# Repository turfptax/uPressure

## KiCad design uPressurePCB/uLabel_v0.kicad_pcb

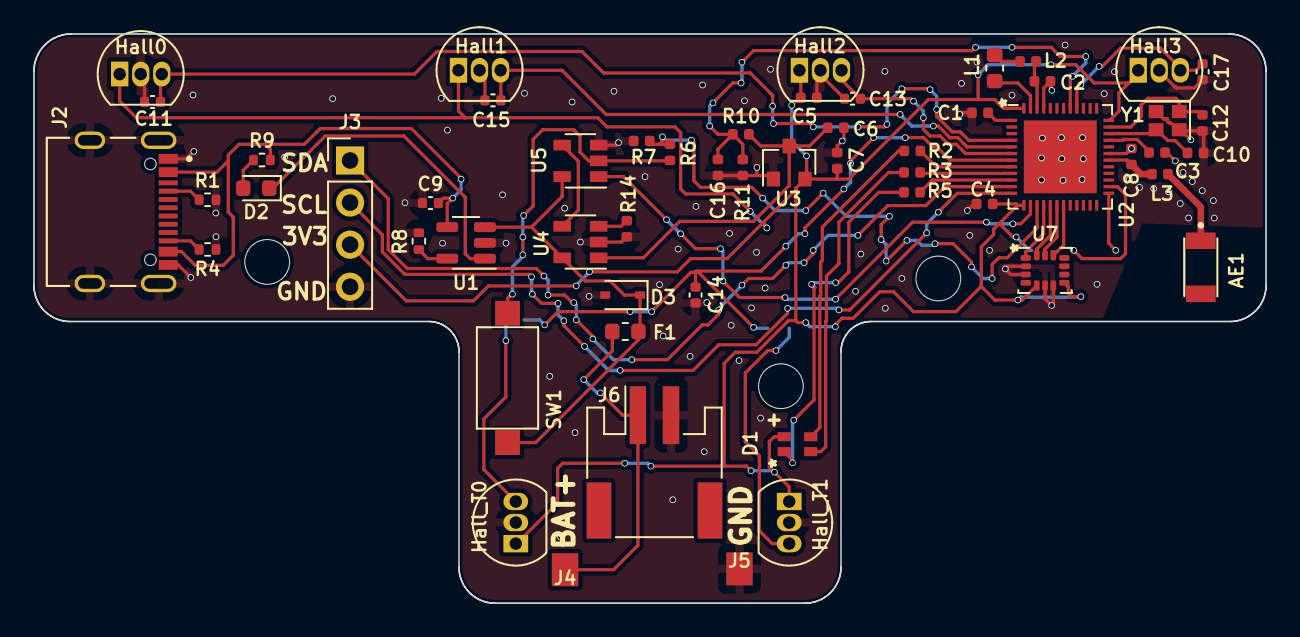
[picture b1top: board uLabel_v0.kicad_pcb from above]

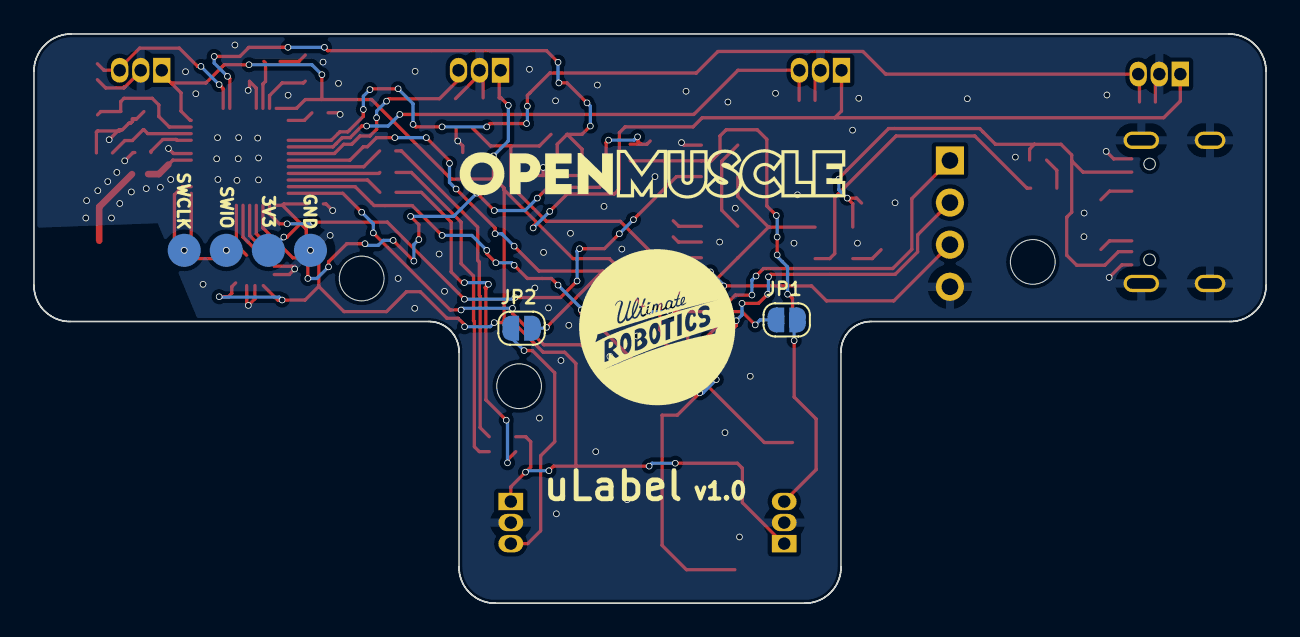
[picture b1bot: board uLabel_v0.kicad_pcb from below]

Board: 2 copper layers, 74.4 x 34.4 mm, 59 parts (3 on the bottom side), 47 nets.

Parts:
AE1: Antenna; KH3216-A55
C1, C4, C11, C13, C14, C15, C16, C17: 100 nF; C_0402_1005Metric
C2, C5, C6, C7, C9: 2.2 uF; C_0402_1005Metric
C3: 100 pF; C_0402_1005Metric
C8: 0.8 pF; C_0402_1005Metric
C10, C12: 12 pF; C_0402_1005Metric
D1: LED_BGRA; LED_RGB_0603_a4
D2: LED GREEN; LED_0603_1608Metric
D3: D; D_SOD-323
F1: Fuse; Fuse_0603_1608Metric
Hall0, Hall1, Hall2, Hall3: DRV5033AJxLPG; TO-92_Inline
Hall_T0, Hall_T1: DRV5033AJxLPG; TO-92_Inline
J2: KH-TYPE-C-16P; KINGHELM_KH-TYPE-C-16P
J3: Scrn_01x04_Header; PinHeader_1x04_P2.54mm_Vertical
J4, J5: Conn_01x01_Male; conn_16_20
J6: Conn_01x02_Female; JST_PH_S2B-PH-SM4-TB_1x02-1MP_P2.00mm_Horizontal
JP1, JP2: SolderJumper_2_Open; SolderJumper-2_P1.3mm_Open_RoundedPad1.0x1.5mm
L1: 10 uH; L_0603_1608Metric
L2: 15 nH; L_0402_1005Metric
L3: 5.1 nH; L_0402_1005Metric
R1, R4, R8: 5.1k; R_0402_1005Metric
R2, R3, R5, R9: 2k; R_0402_1005Metric
R6: 22k; R_0402_1005Metric
R7, R11: 100k; R_0402_1005Metric
R10: 200k; R_0402_1005Metric
R14: 10k; R_0402_1005Metric
SC1: SWD_POGO
SW1: SW_Push; SW_SPST_CK_RS282G05A3
U1: TP4054_replacement_for_MCP73831-2-OT; SOT-23-5
U2: nRF52810-QFxx; QFN-48-1EP_6x6mm_Pitch0.4mm
U3: XC6206P332MR_SOT23; SOT-23
U4: MT9700; SOT-23-5
U5: 74AHC1G32; SOT-23-5
U7: LSM6DS3; LGA-14_3x2.5mm_P0.5mm_LayoutBorder3x4y
Y1: 32MHz; Crystal_SMD_2016-4Pin_2.0x1.6mm

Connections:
+3V3: C4.1, C5.2, C7.2, D1.4 (A), Hall0.1 (VCC), Hall1.1 (VCC), Hall2.1 (VCC), Hall3.1 (VCC), Hall_T0.1 (VCC), Hall_T1.1 (VCC), J3.3, SC1.2 (3V3), U2.13 (VDD), U2.36 (VDD), U2.48 (VDD), U3.2 (VO), U7.5 (VDDIO), U7.8 (VDD)
+3V8: D3.1 (K), F1.1, SW1.2, U1.3 (VBAT), U4.5 (Vin), U5.5 (VCC)
+4V: F1.2, J4.1, J6.1
+5V: C9.2, J2.A4_B9 (VBUS), J2.A9_B4 (VBUS), R9.2, U1.4 (VDD)
+BATT: C6.2, R10.1, U3.3 (VI), U4.1 (Vout)
ADC_H0: C11.2, Hall0.3 (OUT), U2.4 (P0.02/AIN0)
ADC_H1: C15.2, Hall1.3 (OUT), U2.5 (P0.03/AIN1)
ADC_H2: C13.2, Hall2.3 (OUT), U2.6 (P0.04/AIN2)
ADC_H3: C17.2, Hall3.3 (OUT), U2.40 (P0.28/AIN4)
ADC_H4: C14.2, JP1.2 (B), JP2.2 (B), U2.7 (P0.05/AIN3)
BATT_LEVEL: C16.2, R10.2, R11.1, U2.41 (P0.29/AIN5)
BT_OUT: R6.1, SW1.1, U5.2
GND: C1.2, C2.2, C3.2, C4.2, C5.1, C6.1, C7.1, C8.2, C9.1, C10.1, C11.1, C12.1, C13.1, C14.1, C15.1, C16.1, C17.1, D3.2 (A), Hall0.2 (GND), Hall1.2 (GND), Hall2.2 (GND), Hall3.2 (GND), Hall_T0.2 (GND), Hall_T1.2 (GND), J2.A1_B12 (GND), J2.A12_B1 (GND), J2.SH1 (SHIELD), J2.SH2 (SHIELD), J2.SH3 (SHIELD), J2.SH4 (SHIELD), J3.4, J5.1, J6.2, R1.2, R4.1, R7.2, R8.2, R11.2, R14.1, SC1.1 (GND), U1.2 (VSS), U2.31 (VSS), U2.45 (VSS), U2.49 (VSS), U3.1 (GND), U4.2 (GND), U5.3 (GND), U7.2 (SDX), U7.3 (SCX), U7.6 (GND), U7.7 (GND), Y1.2, Y1.4
unnamed: AE1.1 (A), L3.1
unnamed: D1.1 (BK), R5.1
unnamed: D1.2 (GK), R3.1
unnamed: D1.3 (RK), R2.1
unnamed: D2.2 (A), R9.1
unnamed: D2.1 (K), U1.1 (STAT)
unnamed: Hall_T0.3 (OUT), JP1.1 (A)
unnamed: Hall_T1.3 (OUT), JP2.1 (A)
unnamed: J2.A5 (CC1), R1.1
unnamed: J2.B5 (CC2), R4.2
unnamed: L1.2, L2.1
unnamed: R8.1, U1.5 (PROG)
unnamed: C8.1, L3.2, U2.30 (ANT)
unnamed: L1.1, U2.47 (DCC)
unnamed: C1.1, U2.1 (DEC1)
unnamed: C3.1, U2.33 (DEC3)
unnamed: C2.1, L2.2, U2.46 (DEC4)
unnamed: R2.2, U2.8 (P0.06)
unnamed: R3.2, U2.9 (P0.07)
unnamed: R5.2, U2.10 (P0.08)
unnamed: R6.2, R7.1, U2.15 (P0.12)
unnamed: C10.2, U2.34 (XC1), Y1.3
unnamed: C12.2, U2.35 (XC2), Y1.1
unnamed: U4.4 (EN), U5.4
unnamed: R14.2, U4.3 (SET)
SCL: J3.2, U2.12 (NFC2/P0.10)
SDA: J3.1, U2.11 (NFC1/P0.09)
SPI_CS: U2.19 (P0.16), U7.12 (CS)
SPI_SCL: U2.18 (P0.15), U7.13 (SCL)
SPI_SDI: U2.17 (P0.14), U7.14 (SDA)
SPI_SDO: U2.16 (P0.13), U7.1 (SDO/SA0)
SWDCLK: SC1.4 (SWDCLK), U2.25 (SWDCLK)
SWDIO: SC1.3 (SWDIO), U2.26 (SWDIO)
SYS_ON: U2.14 (P0.11), U5.1

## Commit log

2024-02-19 main commit
